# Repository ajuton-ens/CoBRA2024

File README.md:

# CoBRA

Le projet CoBRA (Course de Ballons Réactifs et Autonomes) à pour objectif de construire un ballon dirigeable capable de suivre un parcours de façon autonome et de larguer un colis

## 1 Constitution des équipes

Chaque équipe doit fournir au moins 1 membre à chacun des 4 groupes de travail suivants :
* Préhension & Dépot
* Optimisation de la cinématique de vol
* Modélisation & Contrôle/Commande
* Informatique embarquée & Localisation

## 2 Analyse fonctionnelle et état de l'art
La première séance est consacrée à un travail d'étude générale du problème et d'état de l'art (projet 2023_2024 et autres dirigeables blimp).
* Découper le problème en plusieurs fonctions,
* Pour chaque fonction, spécifier les performances attendues,
* Etudier les solutions retenues en 2023 et les solutions retenues pour d'autres dirigeables,
* Etablir un schéma synoptique du dirigeable.

La semaine suivante, les groupes de travail commenceront leurs études.

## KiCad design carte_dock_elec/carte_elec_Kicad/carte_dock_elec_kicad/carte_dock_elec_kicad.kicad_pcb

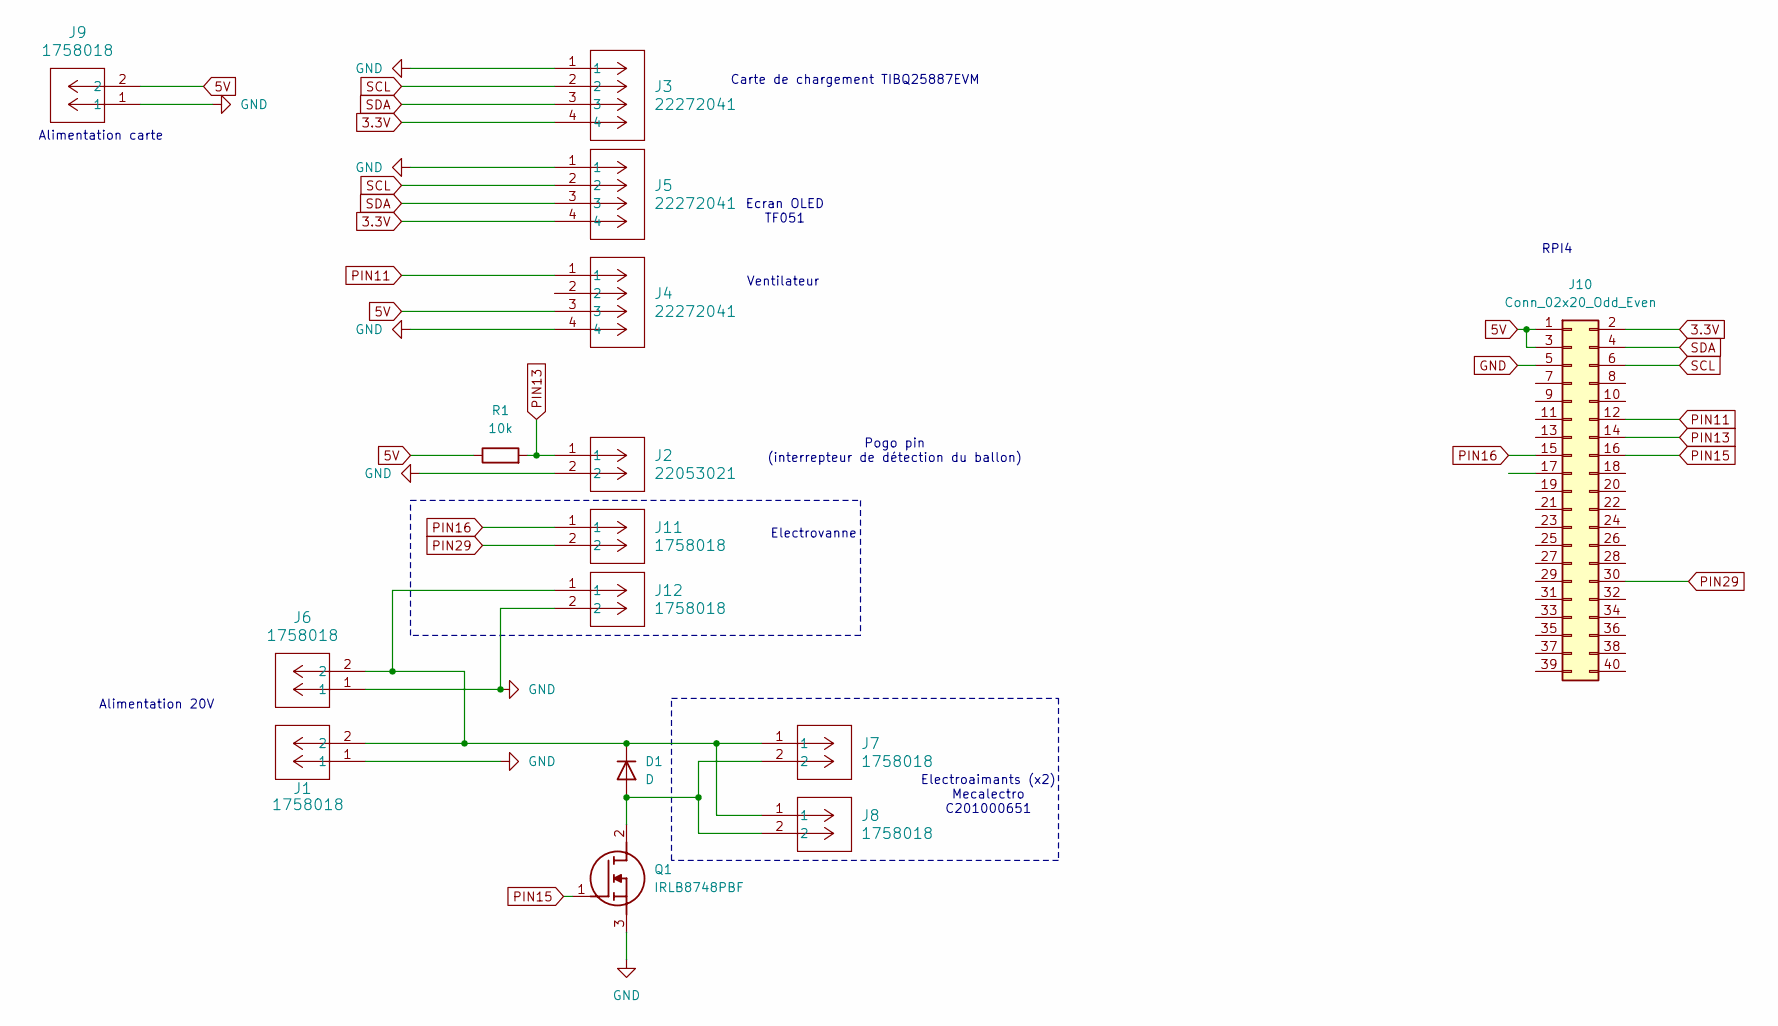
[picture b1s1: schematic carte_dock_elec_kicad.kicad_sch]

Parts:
D1: D; D_1206_3216Metric
J1, J6, J7, J8, J9, J11, J12: 1758018; CONN_1758018
J2: 22053021; CONN_A-7478-02A_MOL
J3, J4, J5: 22272041; CONN_AE-6410-04A_MOL
J10: Conn_02x20_Odd_Even; PinSocket_2x20_P2.54mm_Vertical
Q1: IRLB8748PBF; TO254P483X1016X1994-3P; Manufacturer_Part_Number IRLB8748PBF; Mouser Part Number 942-IRLB8748PBF
R1: 10k; R_1206_3216Metric

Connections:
3.3V: J3.4, J5.4, J10.2
5V: J4.3, J9.2, J10.1, J10.3, R1.1
GND: J1.1, J2.2, J3.1, J4.4, J5.1, J6.1, J9.1, J10.5, J12.2, Q1.3 (S)
unnamed: D1.2 (A), J7.2, J8.2, Q1.2 (D)
unnamed: D1.1 (K), J1.2, J6.2, J7.1, J8.1, J12.1
PIN11: J4.1, J10.12
PIN13: J2.1, J10.14, R1.2
PIN15: J10.16, Q1.1 (G)
PIN16: J10.15, J11.1
PIN29: J10.30, J11.2
SCL: J3.2, J5.2, J10.6
SDA: J3.3, J5.3, J10.4

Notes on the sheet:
Pogo pin (interrepteur de détection du ballon)
Carte de chargement TIBQ25887EVM
Electrovanne
Alimentation carte
Electroaimants (x2) Mecalectro C201000651
Alimentation 20V
RPI4
Ventilateur
Ecran OLED TF051

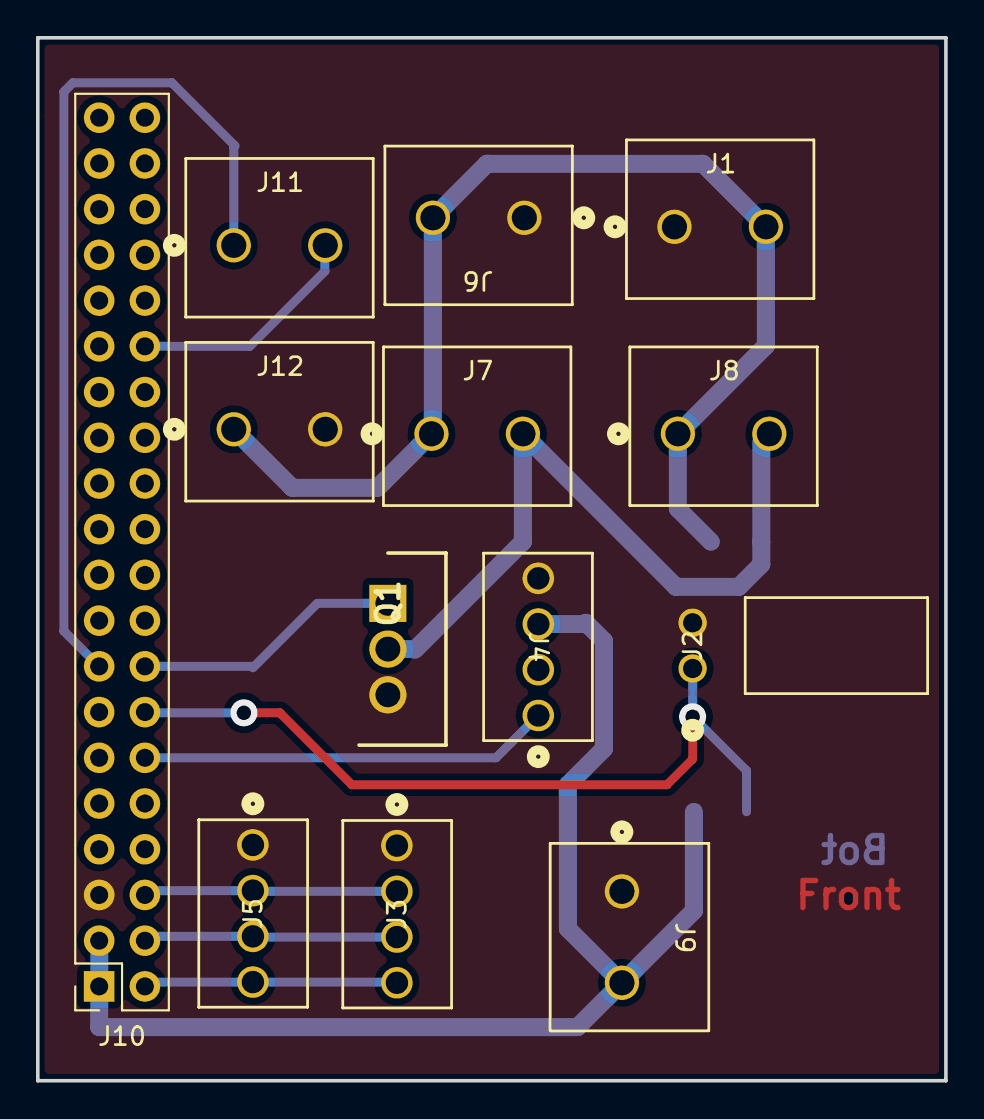
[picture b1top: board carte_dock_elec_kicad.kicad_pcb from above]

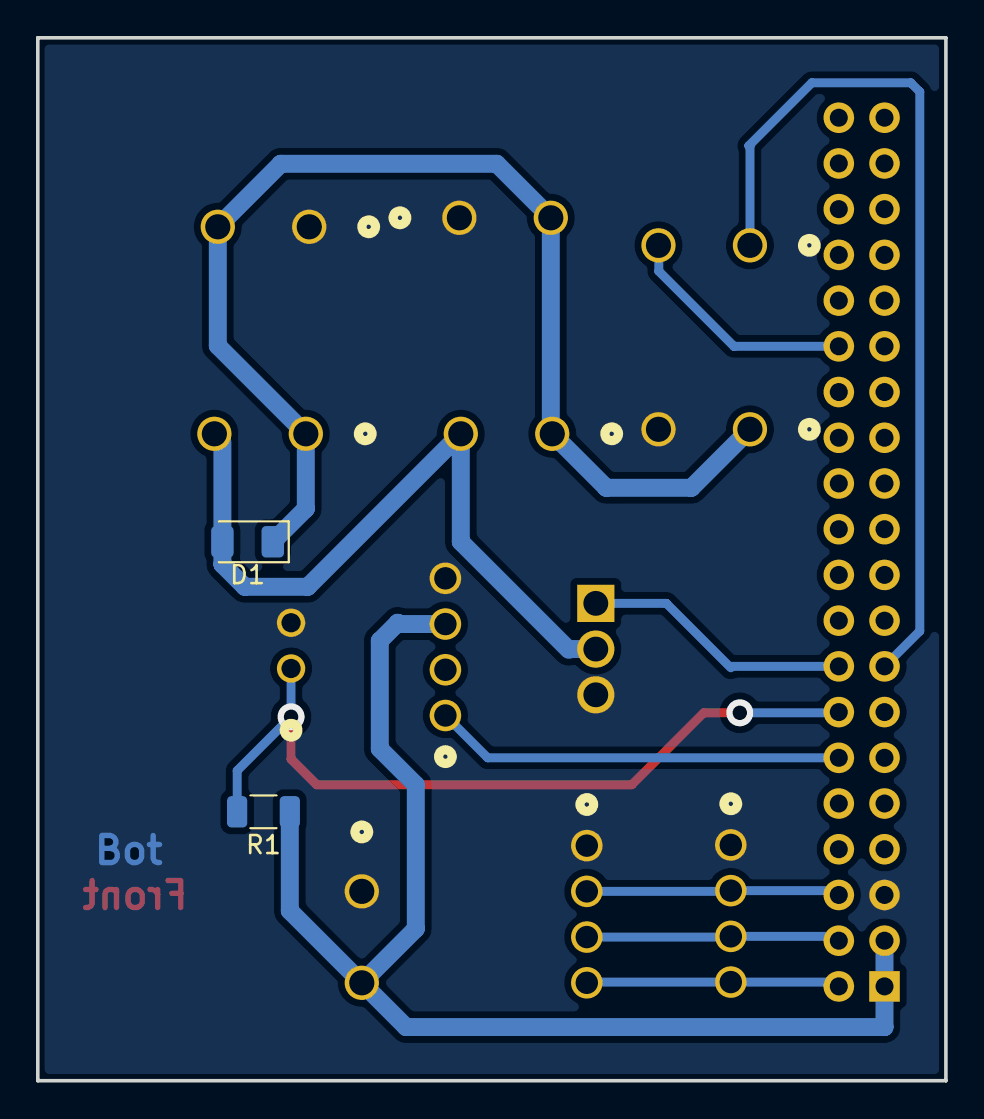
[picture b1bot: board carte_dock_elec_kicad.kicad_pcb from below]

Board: 2 copper layers, 50.5 x 57.9 mm, 15 parts (2 on the bottom side), 12 nets.

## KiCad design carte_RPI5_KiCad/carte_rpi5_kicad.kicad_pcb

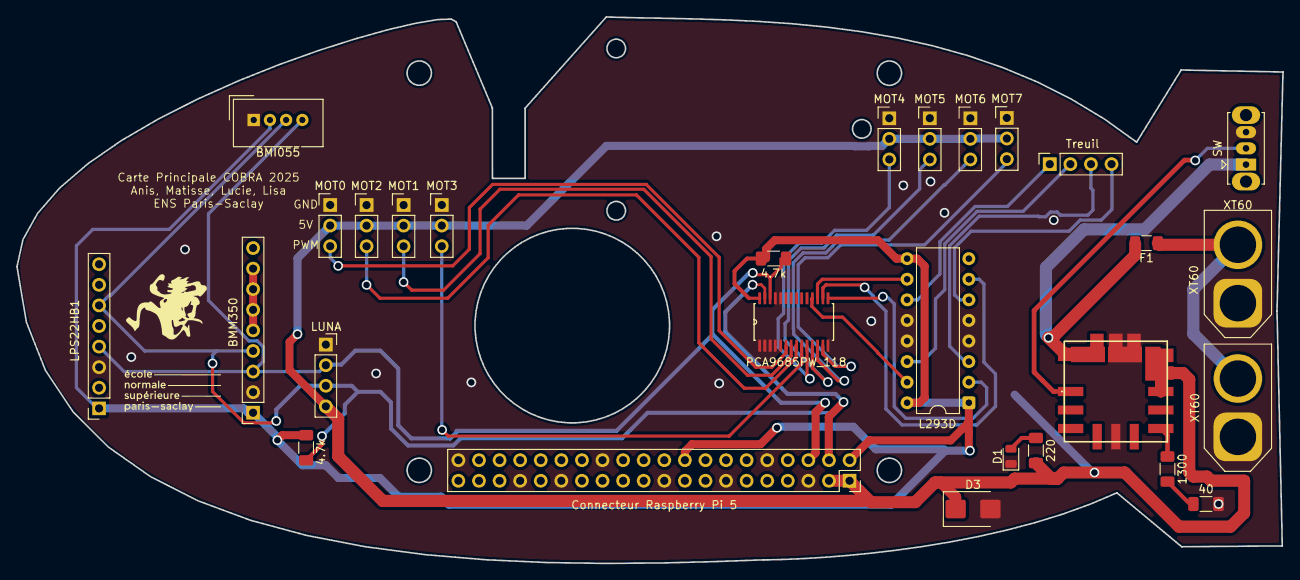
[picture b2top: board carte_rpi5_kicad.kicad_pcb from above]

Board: 2 copper layers, 156.2 x 67.4 mm, 28 parts (0 on the bottom side), 28 nets.

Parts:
4.7k, 4.7k#2: 4,7k; R_1206_3216Metric_Pad1.30x1.75mm_HandSolder
40: 40; R_1206_3216Metric_Pad1.30x1.75mm_HandSolder
220: 220; R_1206_3216Metric_Pad1.30x1.75mm_HandSolder
1300: 1300; R_1206_3216Metric_Pad1.30x1.75mm_HandSolder
BMI055: 110990030; NS-Tech_Grove_1x04_P2mm_Vertical
BMM350: Conn_01x09_Pin; PinSocket_1x09_P2.54mm_Vertical
Contrôleur_PWM1: PCA9685PW_118; SOP65P640X110-28N
D1: LED; LED_0805_2012Metric
D3: Z2SMBxxx; D_SMB
F1: Fuse; Fuse_1206_3216Metric
J10: RPI5_40pins; PinSocket_2x20_P2.54mm_Vertical
L293D: L293D; CERDIP-16_W7.62mm_SideBrazed
LPS22HB1: Conn_01x08; PinSocket_1x08_P2.54mm_Vertical
LUNA: Conn_01x04_Pin; PinSocket_1x04_P2.54mm_Vertical
MOT0, MOT1, MOT2, MOT3, MOT4, MOT5, MOT6, MOT7: Conn_01x03; PinHeader_1x03_P2.54mm_Vertical
Régulateur_de_tension1: OKL-T_6-W12N-C; OKLT6W12NC
SW: SW_SPDT; SW_Slide_SPDT_Straight_CK_OS102011MS2Q
Treuil: Conn_01x04_Pin; PinSocket_1x04_P2.54mm_Vertical
XT60, XT60#2: XT60-M; AMASS_XT60-F_1x02_P7.20mm_Vertical

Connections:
3.3V: 4.7k.2, 4.7k#2.1, BMI055.2, BMM350.1, Contrôleur_PWM1.28 (VDD), J10.2, J10.18, L293D.1 (ENABLE1), L293D.9 (ENABLE2), L293D.16 (VSS), LPS22HB1.1
5V: 220.2, D3.1 (K), J10.1, J10.3, LUNA.4, MOT0.2, MOT1.2, MOT2.2, MOT3.2, MOT4.2, MOT5.2, MOT6.2, MOT7.2, Régulateur_de_tension1.4 (VOUT), Régulateur_de_tension1.5 (SENSE)
GND: 40.2, BMI055.1, BMM350.2, Contrôleur_PWM1.1 (A0), Contrôleur_PWM1.2 (A1), Contrôleur_PWM1.3 (A2), Contrôleur_PWM1.4 (A3), Contrôleur_PWM1.5 (A4), Contrôleur_PWM1.14 (VSS), Contrôleur_PWM1.24 (A5), Contrôleur_PWM1.25 (EXTCLK), D1.1 (K), D3.2 (A), J10.5, J10.10, J10.13, J10.19, J10.26, J10.29, J10.33, J10.40, L293D.4 (GND), L293D.5 (GND), L293D.12 (GND), L293D.13 (GND), LPS22HB1.3, LUNA.1, MOT0.1, MOT1.1, MOT2.1, MOT3.1, MOT4.1, MOT5.1, MOT6.1, MOT7.1, Régulateur_de_tension1.3 (GROUND_1), Régulateur_de_tension1.7 (GROUND_2), SW.3 (C), XT60.1 (NEG), XT60#2.1 (NEG)
Mot_pince+: L293D.11 (OUTPUT3), Treuil.1
Mot_pince-: L293D.14 (OUTPUT4), Treuil.2
Mot_treuil+: L293D.3 (OUTPUT1), Treuil.3
Mot_treuil-: L293D.6 (OUTPUT2), Treuil.4
NC: BMM350.5, BMM350.6, BMM350.7, BMM350.8
unnamed: 220.1, D1.2 (A)
unnamed: F1.1, XT60.2 (POS), XT60#2.2 (POS)
unnamed: 40.1, 1300.2
unnamed: Régulateur_de_tension1.1 (ON/OFF_CONTROL), SW.2 (B)
unnamed: 1300.1, Régulateur_de_tension1.6 (TRIM)
unnamed: F1.2, Régulateur_de_tension1.2 (VIN), SW.1 (A)
PWM0: Contrôleur_PWM1.6 (LED0), MOT0.3
PWM1: Contrôleur_PWM1.7 (LED1), MOT1.3
PWM2: Contrôleur_PWM1.8 (LED2), MOT2.3
PWM3: Contrôleur_PWM1.9 (LED3), MOT3.3
PWM4: Contrôleur_PWM1.10 (LED4), MOT4.3
PWM5: Contrôleur_PWM1.11 (LED5), MOT5.3
PWM6: Contrôleur_PWM1.12 (LED6), MOT6.3
PWM7: Contrôleur_PWM1.13 (LED7), MOT7.3
PWM8: Contrôleur_PWM1.15 (LED8), L293D.2 (INPUT1)
PWM9: Contrôleur_PWM1.16 (LED9), L293D.7 (INPUT2)
PWM10: Contrôleur_PWM1.17 (LED10), L293D.10 (INPUT3)
PWM11: Contrôleur_PWM1.18 (LED11), L293D.15 (INPUT4)
SCL: 4.7k.1, BMI055.4, BMM350.3, Contrôleur_PWM1.26 (SCL), J10.6, LPS22HB1.4, LUNA.2
SDA: 4.7k#2.2, BMI055.3, BMM350.4, Contrôleur_PWM1.27 (SDA), J10.4, LPS22HB1.6, LUNA.3

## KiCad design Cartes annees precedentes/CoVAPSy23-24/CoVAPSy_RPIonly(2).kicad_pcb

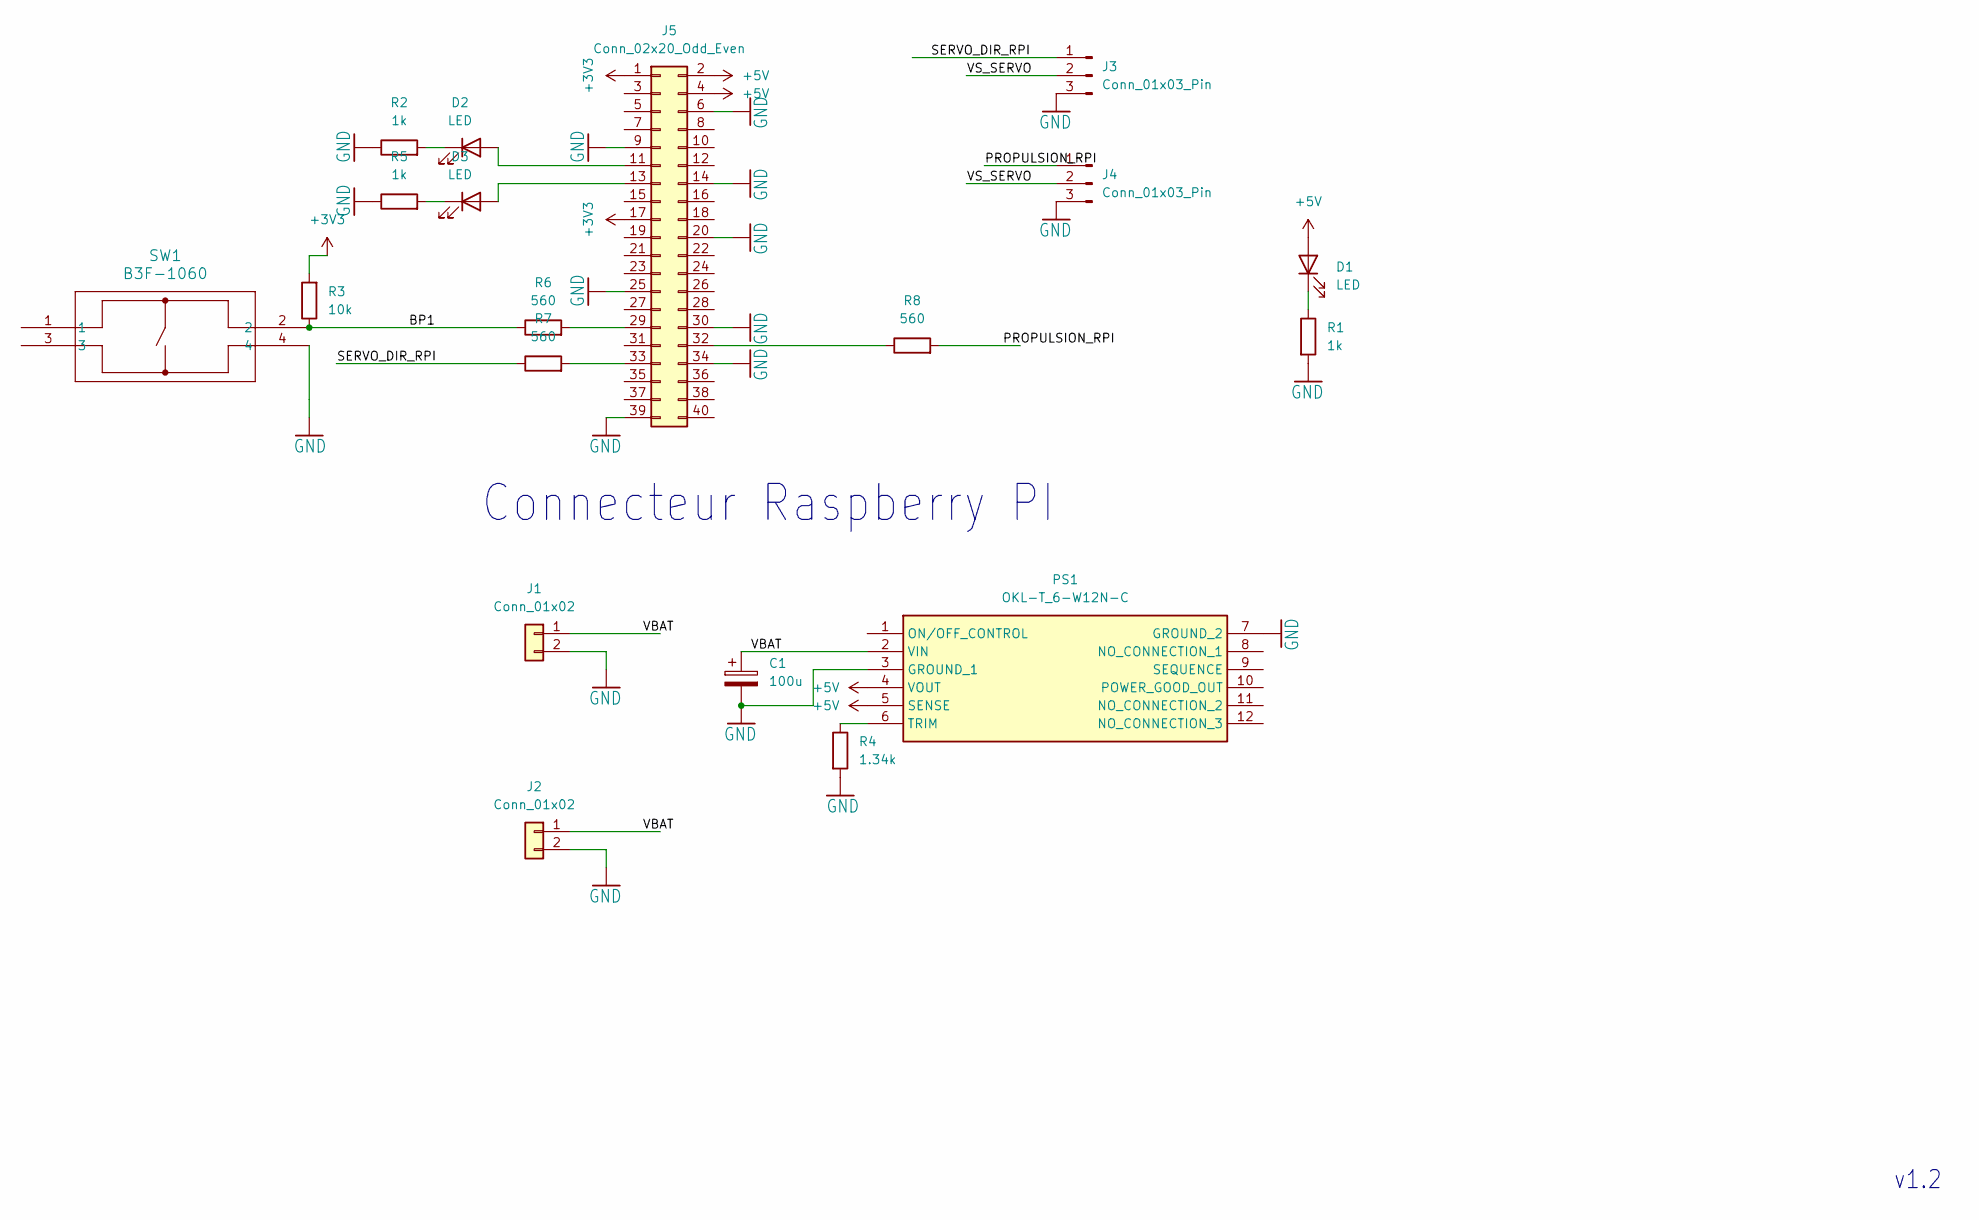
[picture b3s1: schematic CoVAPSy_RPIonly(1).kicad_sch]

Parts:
C1: 100u; CP_EIA-3528-12_Kemet-T_HandSolder
D1, D2, D3: LED; LED_1206_3216Metric_Pad1.42x1.75mm_HandSolder
J1, J2: Conn_01x02; PhoenixContact_MSTBVA_2,5_2-G_1x02_P5.00mm_Vertical
J3, J4: Conn_01x03_Pin; Molex_KK-254_AE-6410-03A_1x03_P2.54mm_Vertical
J5: Conn_02x20_Odd_Even; IDC-Header_2x20_P2.54mm_Vertical
PS1: OKL-T_6-W12N-C; OKLT6W12NC; Mouser Part Number 580-OKL-T/6-W12N-C
R1, R2, R5: 1k; R_1206_3216Metric_Pad1.30x1.75mm_HandSolder
R3: 10k; R_1206_3216Metric_Pad1.30x1.75mm_HandSolder
R4: 1.34k; R_1206_3216Metric_Pad1.30x1.75mm_HandSolder
R6, R7, R8: 560; R_1206_3216Metric_Pad1.30x1.75mm_HandSolder
SW1: B3F-1060; SW_B3F-1060_OMR

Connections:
+3V3: J5.1, J5.17, R3.2
+5V: D1.2 (A), J5.2, J5.4, PS1.4 (VOUT), PS1.5 (SENSE)
/BP1: R3.1, R6.1, SW1.2
/PROPULSION_RPI: J4.1, R8.2
/SERVO_DIR_RPI: J3.1, R7.1
/VBAT: C1.1, J1.1, J2.1, PS1.2 (VIN)
/VS_SERVO: J3.2, J4.2
GND: C1.2, J1.2, J2.2, J3.3, J4.3, J5.6, J5.9, J5.14, J5.20, J5.25, J5.30, J5.34, J5.39, PS1.3 (GROUND_1), PS1.7 (GROUND_2), R1.2, R2.1, R4.2, R5.1, SW1.4
unnamed: D1.1 (K), R1.1
unnamed: D2.2 (A), J5.11
unnamed: D2.1 (K), R2.2
unnamed: D3.2 (A), J5.13
unnamed: D3.1 (K), R5.2
unnamed: J5.29, R6.2
unnamed: J5.32, R8.1
unnamed: J5.33, R7.2
unnamed: PS1.6 (TRIM), R4.1

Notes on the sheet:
v1.2
Connecteur Raspberry PI

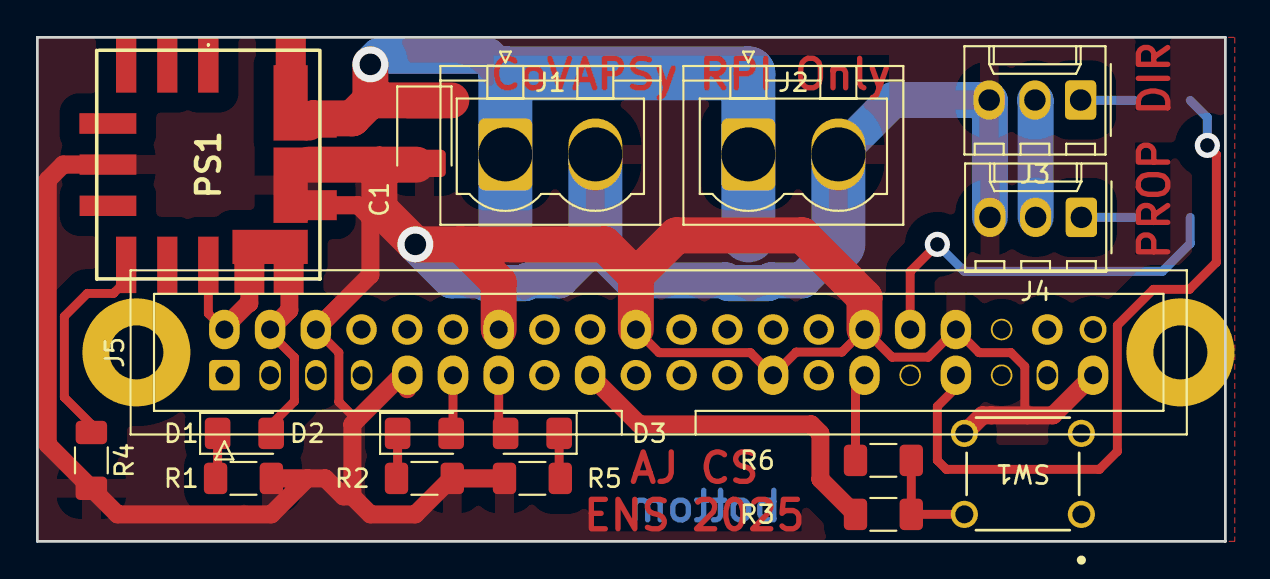
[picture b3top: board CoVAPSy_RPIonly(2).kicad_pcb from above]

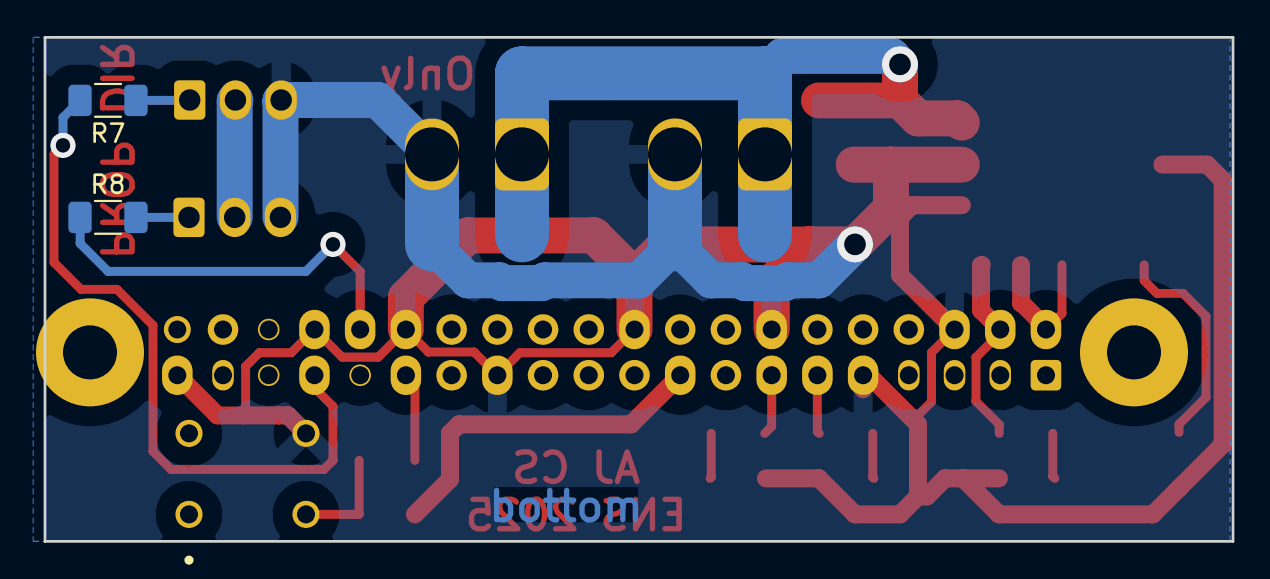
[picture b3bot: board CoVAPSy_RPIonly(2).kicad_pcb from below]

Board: 2 copper layers, 66.0 x 28.0 mm, 21 parts (2 on the bottom side), 17 nets.

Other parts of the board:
UNK_HOLE_0: dummyfp0
UNK_HOLE_1: dummyfp1

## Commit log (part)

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2024-10-01 Update 2024
2024-10-03 Mise à jour 2024
2024-10-11 ajout du tutoriel pour la prise en main de la raspberry Pi Zero
2024-10-11 ajout de test_commandes_PS4.py
2024-10-11 Update Caracteristiques_ballon_constructeur.md
    Lien web vers le site, et non vers la vidéo de présentation
2024-10-11 MAJ du guide d'installation de la RPI zero
2024-10-24 Model_Ctrl_Cmd : ajout mesures altitude echelon
    Modelisation ControleCommande : ajout de mesures MatLab de la réponse du dirigeable en altitude à un echelon (consigne de vitesse du moteur de l'hélice située en dessous du dirigeable). Amplitudes 0.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
2024-10-25 Create 2024_2025
2024-10-25 Ajout de l'article apriltag
2024-10-25 Rename Archives2023_2024/cahier_des_charges.docx to cahier_des_charges.docx
2024-10-25 Create fgh
2024-11-15 Code pour la localisation avec les tags
    J'ai déposé le code pour localiser la caméra en utilisant les tags
2024-11-15 Update DetectTagPi5
    Ajout des commentaires
2024-11-15 Update DetectTagPi5
2024-12-06 Add files via upload
    Variateur AM16AT
2024-12-15 Create bibliographie
2024-12-15 Update bibliographie
2025-01-10 Create Presentations_solutions_techniques
2025-01-10 modifications
2025-01-10 présentation demandé par les professeurs
2025-02-05 Deleting DetectTagPi5, necessité de l'adaptation pour deux caméras
2025-02-07 Create CarteElec2024
2025-03-14 Creation du dossier bibliotheques2024_2025
2025-03-28 Version v02 de la commande du generateur PWM
    commande moteurs
2025-03-28 Version v03 de la commande du generateur PWM
    commande moteur brushless. Pas encore implemente MCC
2025-03-28 Version v03 de la mesure du TFLUNA
    capteur telemetre distance TFLUNA
2025-04-11 Versions v04 et v05 de la commande du generateur PWM
2025-04-11 Version v06 de la commande du generateur PWM
2025-05-09 Version v09 de la commande du generateur PWM
2025-05-16 Version v12 de la commande de tous les moteurs
2025-06-07 Ajout des posters
2025-06-10 ajout des rapports
2025-06-10 version de 2025.06.10 du code final
    Dossier 2025.06.10 testé pendant la séance
    Dossier 2025.06.10_chezmoi pas testé, codé après la séance : contient asservissement x,y,z sans asservissement de l'angle heading (c.à.d. l'angle yaw)
2025-06-11 version de 2025.06.11 du code final
    Dossier 2025.06.11 testé pendant la séance
2025-06-12 version de 2025.06.11 du code final (chez moi)
    Dossier 2025.06.11_chezmoi PAS testé
2025-06-12 version de 2025.06.12 du code final (en attendant)
    Dossier 2025.06.12_enattendant PAS testé
2025-06-13 CoBrasCasses : Code entier
2025-10-08 Create READ_ME
2025-10-08 Rename READ_ME to READ_ME.txt
2025-10-08 Rename READ_ME.txt to READ_ME
2025-10-10 Add Tutoriel_Kicad_v1.pdf
2025-10-10 Add LIB_OKL-T_6W12N-C.zip
2025-10-11 Put KiCad Tutoriel in its directory
2025-11-07 clean branch
2025-11-07 add archi.md
2025-11-07 create blank kicad project
2025-11-07 Deleting history
2025-11-07 ajout des docs constructeur du ballon
2025-11-07 rangement...
2025-11-07 Revise objectives and control strategy in readme
    Updated the objectives and control/command sections to include parameter identification and simulation testing.
2025-11-07 Update avancement.md with October progress details
    Added updates on modeling and control progress for October.
2025-11-07 Update avancement.md with progress questions
    Added questions regarding the progress and functionality of programs.
2025-11-07 ajout essais asservissement 202506
2025-11-07 ajout du dossier 20252026
2025-11-07 Revise README for 2025-2026 progress updates
    Updated the README to reflect progress and changes for 2025-2026, including updates on localization solutions and sensor integration.
2025-11-07 datasheets + archi update
2025-11-07 archi capteur pression
2025-11-07 Update avancement.md with November progress notes
    Added notes on progress and issues encountered in November.
2025-11-07 Update avancement.md with november 7th
    Clarified the work on 'lacet' with motor direction details.
2025-11-14 update architecture
2025-11-14 mise à jour archi
2025-11-14 update architecture rp5
2025-11-14 Add mech drawing RPi5
2025-11-14 Update Readme with project advancements
    Added updates on camera testing and GPS Indoor.
2025-11-14 Update Readme with Apriltag spacing analysis
    Added analysis of Apriltag spacing to video stream access notes.
2025-11-19 Ajout de l'article culture sciences de l'ingénieur
2025-11-19 renommage de la partie livrable janvier 2025
2025-11-21 dépot des empreintes
2025-11-21 Update avancement.md with PID settings
    Added PID parameters for control in the document.
2025-11-21 Add BNO055, OKL-T-6 and LPS22HB
2025-11-21 depot empreintes
2025-11-21 Mise à jour symboles et empreintes
2025-11-21 Placement composants
2025-11-21 Add architechture dock
2025-11-21 Début du schéma Kicad
2025-11-21 Add empreinte BNO055_version_pas_en_surface
2025-11-21 Create Vslam
2025-11-28 Add Rapports annes precedentes
2025-11-28 Add empreinte BNO055 pour prototype
2025-11-28 Modif kicad
2025-11-28 Rename Regulateur_tension_bonne_empreinte
2025-11-28 Add telemetre LUNA to architechture_carte_rpi5
2025-11-28 Update motor pin assignments and test library
    Updated motor pin assignments and tested library version.
2025-11-28 Kicad edit
2025-12-01 Ajout des cartes électroniques 2025
2025-12-05 kicad
2025-12-05 Add cartes annees precedentes
2025-12-05 Modify empreinte OKLT6
2025-12-05 Empreinte OKL ok
2025-12-05 Ajoute empreinte xt60
2025-12-05 ajout_empreinte_modele3D
2025-12-05 Add empeintes to carte_rpi5
2025-12-05 Update architechture carte
2025-12-05 pcb_V0.1
2025-12-05 mise à jour PCB
2025-12-10 Ajout d'un article RL/Blimp/Gazebo
2025-12-12 Add pi5-active-cooler.step in Modele 3D
2025-12-12 Add 4628 - porte fusible to empreintes
2025-12-12 Mise à jour du PCB
2025-12-18 Deuxième version du routage pour le PCB
    Il y a encore pas mal d'erreurs au niveau des pads, voir la taille minimale acceptable des pistes pour chaque composant.
2025-12-19 Agrandissement + recablage du PCB
2025-12-23 Mise à jour PCB
    Correction des erreurs sur les pistes / via, ajouts de sérigraphie, logos et vérification du PCB, il reste malgré tout une erreur indiquant que les deux plans de masses de sont pas reliés même avec l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
2025-12-26 Finalisation du PCB
    Toutes les erreurs DRC ont été corrigés. Le PCB est prêt à être tiré.
    Anis.
2026-01-06 Carte modification version finale
2026-01-08 Ajout_schema_carte
2026-01-08 Réorganisation0801
2026-01-08 Modif_schema_synoptique
2026-01-08 fichier_changement_nom
2026-01-09 Ajout Présentation Méca Dirigeable
2026-01-10 Ajout_nw_schema_synoptique
2026-01-30 changement_sens_connecteur_RPI
2026-01-30 modif_plan_masse
2026-02-09 modif PCB 06/02
2026-02-13 modif_PCB_ajout_resistance
2026-02-13 Ajout_fichiers
2026-02-20 Add initial content for CoBRA components documentation
2026-02-20 Add propeller details to composantsCobra.md
    Added propeller information for the CoBRA dirigible.
2026-02-20 Add price for AS2303 F3P motors
2026-02-20 Add link for AS2303 F3P motor
    Added a link for the AS2303 F3P motor specifications.
2026-02-20 Modify propeller details in composantsCobra.md
    Updated the propeller information with a new price and link.
2026-04-03 Ajout_fichier_carte_capteur_pression
2026-04-03 Add carte dock
2026-04-03 add carte
2026-04-03 MAJ_fichier_dock_helium
2026-04-03 MAJ_carte_dock_helium
2026-04-03 ajout_librairie_ESP328devboard
2026-04-10 Creation_fichier_carte_dock_elec
2026-04-10 Codes_capteur_pression_et_ESP32
2026-04-10 Schema_de_cablage_ESP32_LPS22
2026-04-10 Modif_carte_elec
2026-04-17 h
    h
2026-04-17 Modif_schema_creationPCB
2026-04-17 Update composantsCobra.md with new components
    Added ESC, LiDAR, accelerometer, and pressure sensor details.
2026-04-17 carte_dock
2026-04-17 ajout_carte_rpi5
2026-04-17 carte_dock_helium
2026-05-22 mise à jour
2026-05-22 Create Programmes_Eloi
2026-05-22 Create test
2026-05-22 Update BLE Program
2026-05-22 MAJ DOCK ELEC
2026-05-22 Rename libraires_externes.txt to .info_libraires_externes.txt
2026-05-22 Rename asserv_h_2025.py to main.py
2026-05-22 Update BLE Arduino and Python Programs
2026-05-22 maj carte
2026-05-23 modif carte_dirigeable
2026-05-23 modif2_carte_dirigeable
2026-05-29 modif PCB_carte_doc
2026-05-29 Update codes Capteur Pression
2026-05-29 modif1
2026-06-04 Modif_carte_dock
2026-06-04 rapport
2026-06-07 modif_carte_dick
2026-06-15 Add readme for camera calibration automation
    Added information about automated camera calibration process.
2026-06-15 Rename readme2 to readme2.md
2026-06-15 Update readme2.md for camera calibration details
    Clarified the process of camera calibration and photo capture.
2026-06-15 Create readme2.md with usage instructions
    Added usage instructions for Adam_2026 codes and related scripts.
